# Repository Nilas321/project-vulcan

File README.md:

# Project VULCAN

A project in which we aim at making a humanoid robot's facial structure that can interact with humans and have some simple skills and interactions.

## Usage of this project

*	The main use of this robot is to be an assistant just like Alexa and other assistants... So, then what is the difference? well... this robot will give a human interactive and fell to the answers it... so it feels as if you are conversating with a human and not a speaker ... 
*	Planning to use a good camera with a decent FOV as we need to track the humans around it so the precision will be needed... 

## Major Features

We aim this bot to have facial movements like humans and also have expressions. 

Elaborating:

```
*	Eyeballs moving and having eye contact with the person to be interacted.
*	Mouth moving when the robot speaks.
*	Eyebrow movements.
*	Neck movement.
*	Hearing and speaking.
*	2 cameras in the eyes for vision.
*	Analysing what the person has spoken and given a sensible reply... trying to integrate with google, Wikipedia and other platforms that can give a good answer for a question.
```

### Going deeper into the motions

```
*	Each eyeball having independent motion in 2 axes.
*	Each eyeball having an eyelid that can open and close.
*	Eyebrows that can up-down to add to the expressions.
*	Mouth that can bring about expressions with lips.
*	Neck motion to move the entire system about 2 axes.
```

## Sensing

*	Camera for human detection and other things in the environment.
*	Microphones for sound detection and locating the sound source.

## Subsystems

### Mechanical
*	[Eye, eyelid and eyebrow subsystem](https://www.youtube.com/watch?v=uqxhR49N3ws): Eyeballs non symmetric motion with cameras in each. Eyelids opening and closing. Eyebrows for motion.
*	[Mouth subsystem](https://www.youtube.com/watch?v=Ke2lJfY4haM):  . Movement while delivering words and also depicting emotions through lips.
*	[Neck subsystem](https://www.youtube.com/watch?v=GJRW8hP-Jcs):  . 360-degree motion in horizontal plane and up-down in vertical plane.

### Coding

*	Movement of all mech subsystems: Coordination of all servos and other actuators to bring about emotions and other functions like talking.
*	Hearing and Speech production: Speech recognition, processing it and delivery of words and emotions to the above system. NLM, NLP. 

## Limitations
*	Cannot move physically, just creating the structure above the neck.

## The future of this project?

Well... this is probably the 1% out of the 100 that we can do with... can start another project with bi-paddle motion and mount this on top of it?? and with the robotic arms?? or just the robotic arms??? well that quite open for now... but this is a crucial step as we will be making the so called "head".

## Present existence of similar projects:

*	At present the best example of such a project is Sophia robot, kismet, Ameca robots ... we aim to reach closer to that by this project...

*	However, our robot just comprises of the face but still, it can serve the purpose we aim to make it for... 

*	We have seen many big companies build humanoid robots but a robot that can move and come to use in daily life but starting this at college level would be amazing...

## Built With

* [Python](https://www.python.org/) - The language used
* [ROS](https://www.ros.org/) - Environment used
* [OPENCV](https://opencv.org/) - Used for vision

## Contributers

* [Parth Shah](https://github.com/Parth-Shah-Tool-Kit) - Project lead
* [Ritwik Sharma](https://github.com/Maker-Rat) - Project lead

### Coding and Electronics team
* [Ajinkya Deshpande](https://github.com/ajinkya110001)
* [Nayan Gogari](https://github.com/NG2411)
* [Param Gandhi](https://github.com/Pamdi8888)
* [Sharvil Potdar](https://github.com/SMP111  )
* [Vimarsh Shah](https://github.com/vimarsh244)
* [Nilay Wani](https://github.com/Anymal2408)

### Mech team
* [Atul M](https://github.com/RoboAM13)
* [Nilay Wani](https://github.com/Anymal2408)
* [Padi Sudeep](https://github.com/WhatRaSudeep)

### X Members
* [Mehlam Songerwala](https://github.com/mehlams)
* [Naitik Verma](https://github.com/07naitik)
* [Vrishti Godhwani](https://github.com/Vierra11)
* [Shloka Shetty](https://github.com/shloka15)

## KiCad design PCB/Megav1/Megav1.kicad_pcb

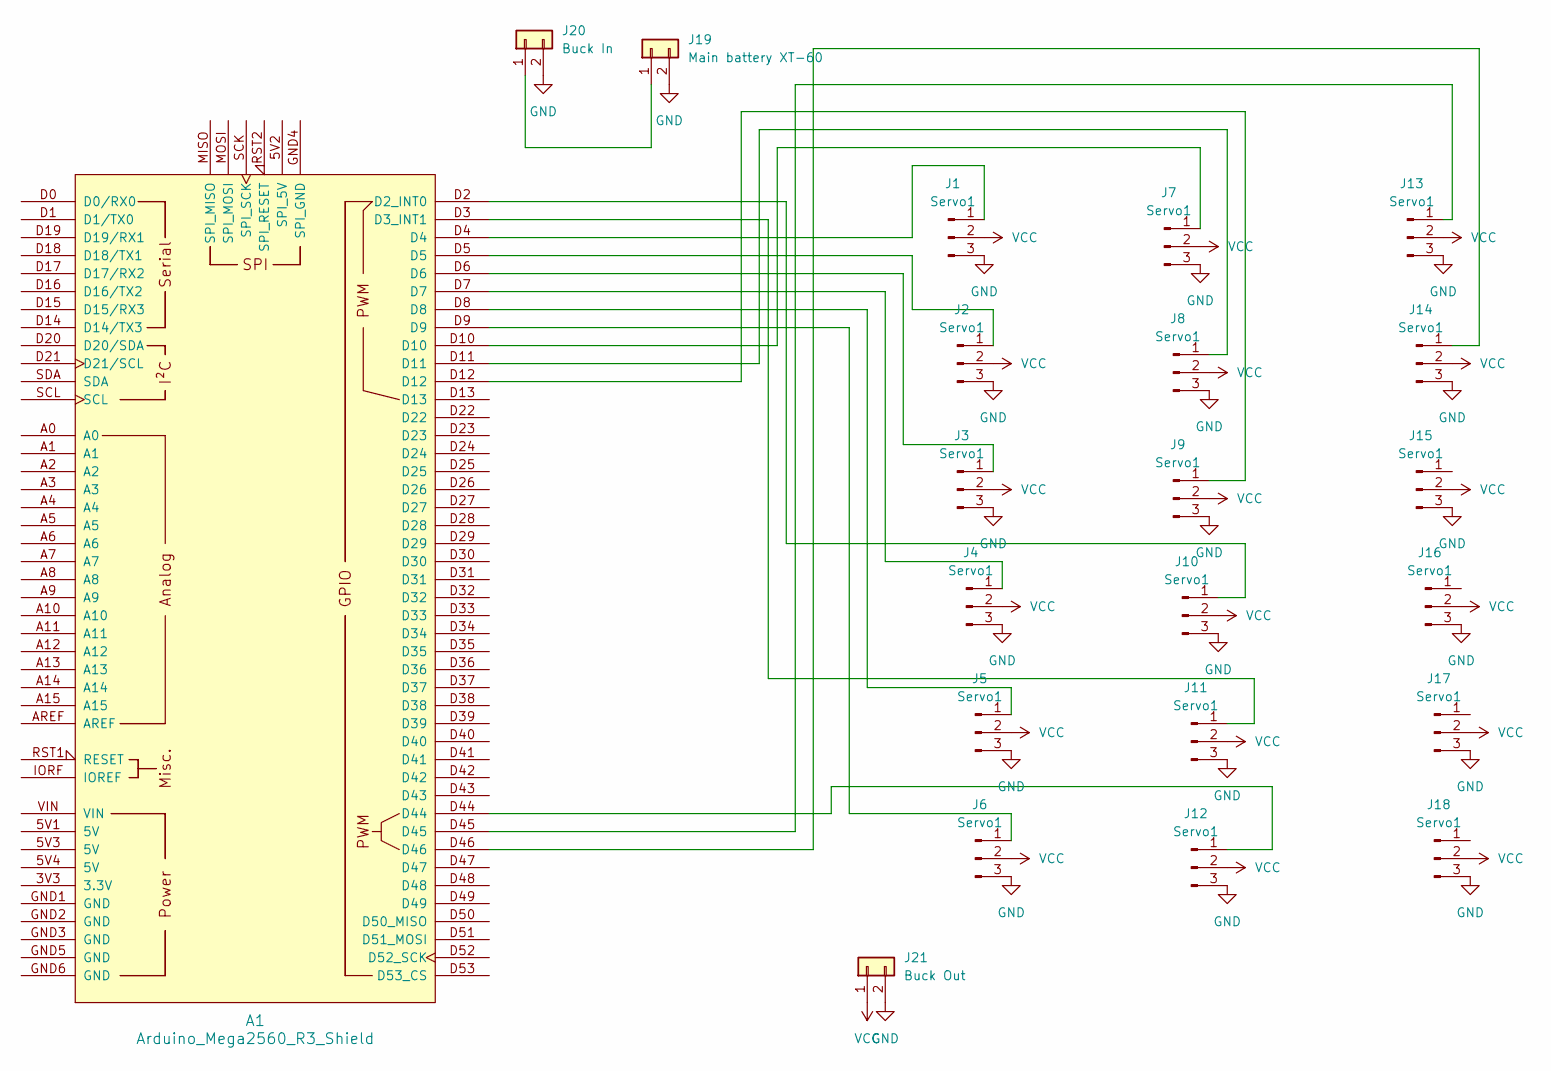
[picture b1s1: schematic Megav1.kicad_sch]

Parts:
A1: Arduino_Mega2560_R3_Shield
J1, J2, J3, J4, J5, J6, J7, J8, J9, J10, J11, J12, J13, J14, J15, J16, J17, J18: Servo1; FanPinHeader_1x03_P2.54mm_Vertical
J19: Main battery XT-60; AMASS_XT60-F_1x02_P7.20mm_Vertical
J20: Buck In; AMASS_XT60-F_1x02_P7.20mm_Vertical
J21: Buck Out; AMASS_XT60-F_1x02_P7.20mm_Vertical

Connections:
GND: J1.3, J2.3, J3.3, J4.3, J5.3, J6.3, J7.3, J8.3, J9.3, J10.3, J11.3, J12.3, J13.3, J14.3, J15.3, J16.3, J17.3, J18.3, J19.2, J20.2, J21.2
unnamed: A1.D2 (D2_INT0), J10.1
unnamed: A1.D3 (D3_INT1), J11.1
unnamed: A1.D4, J1.1
unnamed: A1.D5, J2.1
unnamed: A1.D6, J3.1
unnamed: A1.D7, J4.1
unnamed: A1.D8, J5.1
unnamed: A1.D9, J6.1
unnamed: A1.D10, J7.1
unnamed: A1.D11, J8.1
unnamed: A1.D12, J9.1
unnamed: A1.D44, J12.1
unnamed: A1.D45, J13.1
unnamed: A1.D46, J14.1
unnamed: J19.1, J20.1
VCC: J1.2, J2.2, J3.2, J4.2, J5.2, J6.2, J7.2, J8.2, J9.2, J10.2, J11.2, J12.2, J13.2, J14.2, J15.2, J16.2, J17.2, J18.2, J21.1

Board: 2 copper layers, 22 parts (0 on the bottom side), 17 nets, no tracks yet.

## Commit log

2023-05-28 Added README.md
2023-05-28 Create cv_expression_test
2023-06-01 Rename proper install of cuda with cv2 and dlib.txt to proper install of cuda with cv2 and dlib..md
2023-06-01 Update and rename proper install of cuda with cv2 and dlib..md to proper install of cuda with cv2 and dlib.
2023-08-05 Add files via upload
    I guess this works better than earlier one..
2023-08-19 Update and rename proper install of cuda with cv2 and dlib. to how to install cuda for cv2 and dlib
2023-09-04 Rename kaash_ye_chal_jaaye.py to active speaker(final).py
2023-09-06 show how to commit
2023-09-06 add docs
2023-10-18 local function calling works
2023-10-18 Stopped tracking env
2023-10-18 Added Link to Download Shape Predictor Dat File
2023-10-18 instruction for mic
2023-10-18 Create check_mic
2023-10-18 Rename check_mic to check_mic.py
2023-10-21 add function calling
2023-11-01 Added active speaker arduino.ino
2023-11-05 pcb in the making
2023-11-05 it blinks!!!
2023-11-05 shoudl work
2023-11-08 After Open day, with expressions.
2024-01-17 Create speaker_ros.py
    I added ROS publishers for 'faces' and 'speakers'.
    The detected faces and speakers are published as ROS messages.
2024-01-30 Text To Speech
2024-02-10 add stiching images support
